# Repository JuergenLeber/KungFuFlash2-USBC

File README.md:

# Kung Fu Flash 2 USB-C

Cartridge for the Commodore 64 that packs a punch.

This repository is a fork of [KungFuFlash2-USBC](https://github.com/Sgw32/KungFuFlash2-USBC) which is a fork of an earlier version of [KungFuFlash2](https://codeberg.org/KimJorgensen/KungFuFlash2) from Kim Jørgensen that was later moved to Codeberg and is still being updated.

To have the "best of both worlds" (USB-C and updated firmware) this repository merged both of them together and additionally introduces some small fixes to the PCB and the production files.

Kung Fu Flash 2 is the big brother of [Kung Fu Flash](https://codeberg.org/KimJorgensen/KungFuFlash). It has a faster microcontroller with more memory and I/O pins, allowing for additional functionality.

**Currently, this project is considered experimental** and provides the same features as Kung Fu Flash, with these notable exceptions:

* CRT files are loaded into RAM, not flash, making large CRT files startup faster. However, changes to EasyFlash cartridges are lost if power is turned off, unless saved via the menu first
* The cartridge detects if the C64/C128 is reset. This allows the use of an additional reset button on the C64 or the built-in reset button on the C128
* REU emulation has been added

Kung Fu Flash 2 can emulate different cartridge types, load PRG files and use D64 disk images.
Just place your desired CRT, PRG or D64 files on a FAT formatted microSD card and use the built-in launcher to execute them.

## Hardware

There are three buttons on the cartridge; a reset button, a menu button for starting the launcher, and a special button that is used by the freezer cartridges.

A very nice case has been designed by [Bigby](https://www.printables.com/@Bigby) and can be found on [Printables](https://www.printables.com/model/119330-kung-fu-flash-cartridge-case).

(Picture shows the old version and will be updated as soon as the new prototypes arrive)

The gerber files and BOM can be found [here](./hardware/gerber/).

## Supported Cartridges

The following cartridge types are currently supported:

* Generic cartridge (8k, 16k, Ultimax)
* Action Replay v4.x/v5/v6
* KCS Power Cartridge
* Final Cartridge III(+)
* Simons' BASIC
* Fun Play, Power Play
* Super Games
* Ocean type 1
* Epyx Fastload
* C64 Game System, System 3
* WarpSpeed
* Dinamic
* Zaxxon, Super Zaxxon
* Magic Desk, Domark, HES Australia
* Super Snapshot v5
* Comal-80
* Ross
* EasyFlash
* Prophet64
* Freeze Frame
* Freeze Machine
* MACH 5
* Pagefox
* RGCD, Hucky
* Drean
* C128 Generic cartridge (external function ROM)
* WarpSpeed 128

## Supported File Types

The following file types are currently supported:

* Cartridge (CRT)
* C64/C128 generic cartridge (ROM, BIN)
* Disk image (D64, D71, D81)
* Tape image (T64)
* Program (PRG, P00)
* SID tune (SID)
* Firmware update (UPD)
* Text document (TXT, NFO, 1ST)

## SID Playback

SID tunes can be played directly from the launcher. This feature is inherited from the
[KungFuFlash2-USBC](https://github.com/Sgw32/KungFuFlash2-USBC) fork and is not part of the original Kung Fu Flash 2.

Selecting a SID file in the file options menu offers two actions:

* "Play" (RETURN) converts the tune and starts it immediately
* "Convert to PRG" (SHIFT+RETURN) writes a PRG file next to the SID file and returns to the launcher

In both cases the tune is converted to a PRG containing a small BASIC starter and a raster interrupt player,
so the resulting file can also be used on any other C64 setup. As the PRG is written to the microSD card,
the card must not be write protected.

PSID and RSID files of version 1 to 3 are supported, with these limitations:

* Only the first subtune is played; the tune and subtune information from the SID header is ignored
* The player uses a single speed raster interrupt, so multi speed tunes will play at the wrong tempo
* Tunes that load below $0843 cannot be converted, as this area is occupied by the BASIC starter and the player

## REU Emulation

Kung Fu Flash 2 can emulate a 1 Mb REU (RAM Expansion Unit) simultaneously with disk drive emulation.
The REU is enabled in the settings menu (F5) and active when:

* A program is executed using the default option (RETURN)
* A disk image or directory is mounted using "Mount" in the file options menu (SHIFT+RETURN)
* BASIC is started via F6 (C128) or F7 (C64) in the launcher

The REU will not be active when emulating cartridges (CRT files)

## USB Port

The USB port allows programs or disk images to be transferred from/to a PC using the EasyFlash 3 USB protocol.
The USB port is active when:

* The Kung Fu Flash 2 launcher is running
* A program is started using "Load" in the file options menu (SHIFT+RETURN)
* BASIC is started via F7 in the launcher **and** REU emulation is disabled in the settings menu (F5)

Kung Fu Flash 2 shows up as a standard serial port when connected to a PC not requiring any custom drivers to be installed.
This means, however, that the EasyFlash 3 program on the PC side must be modified to support Kung Fu Flash.

The repository of the original Kung Fu Flash contains a modified version of [EasyFlash 3 USB Utilities](https://codeberg.org/KimJorgensen/KungFuFlash/src/branch/master/3rd_party/ef3utils)
and [EasyFlash 3 BBS](https://codeberg.org/KimJorgensen/KungFuFlash/src/branch/master/3rd_party/ef3bbs) which will also work with the Kung Fu Flash 2.

## Firmware Update

Just place the KungFuFlash2_v2.xx.upd file on the SD card and select the file in the launcher to initiate the firmware update.
The newest firmware can be found [here](https://github.com/JuergenLeber/KungFuFlash2-USBC/releases).

For initial firmware installation, [see here](firmware/README.md).

## Limitations

Kung Fu Flash 2 is a so called Software Defined Cartridge where a fast microcontroller emulates cartridge hardware in software.
This makes it extremely flexible, allowing different cartridge types to be supported at a relative low cost.

However, it can be challenging to get the C64 bus timing correct in software and in some places the timing is very close to the limit.
Even though Kung Fu Flash 2 has been tested on different models of the Commodore 64, there is a chance that it doesn't work correctly on your specific model, or requires [phi2 offset adjustment](firmware/README.md#diagnostic).
Use it at your own risk!

Kung Fu Flash 2 will work with the PAL and NTSC version of the Commodore 64 or Commodore 128.

Disk drive emulation is using kernal vectors and will not work with fast loaders or software that uses direct hardware access which a lot of games does.
Currently REL files are not supported and only a subset of the Commodore DOS commands are supported.

## Thanks

Kung Fu Flash 2 was based on or uses other open source projects:

* [Kung Fu Flash](https://codeberg.org/KimJorgensen/KungFuFlash)
* [EasyFlash 3](https://bitbucket.org/skoe/easyflash) by Thomas Giesel
* [Draco Browser](https://csdb.dk/release/?id=89910) by Sascha Bader
* [fatfs-stm32](https://github.com/colosimo/fatfs-stm32) by Aurelio Colosimo
* [FatFs](http://elm-chan.org/fsw/ff/00index_e.html) by ChaN
* [libusb_stm32](https://github.com/dmitrystu/libusb_stm32) by Dmitry Filimonchuk
* [OpenC64Cart](https://github.com/SukkoPera/OpenC64Cart) by Giorgioggì
* [Disk2easyflash](https://csdb.dk/release/?id=150323) by ALeX Kazik

and a few others. Please check the individual files for their license.

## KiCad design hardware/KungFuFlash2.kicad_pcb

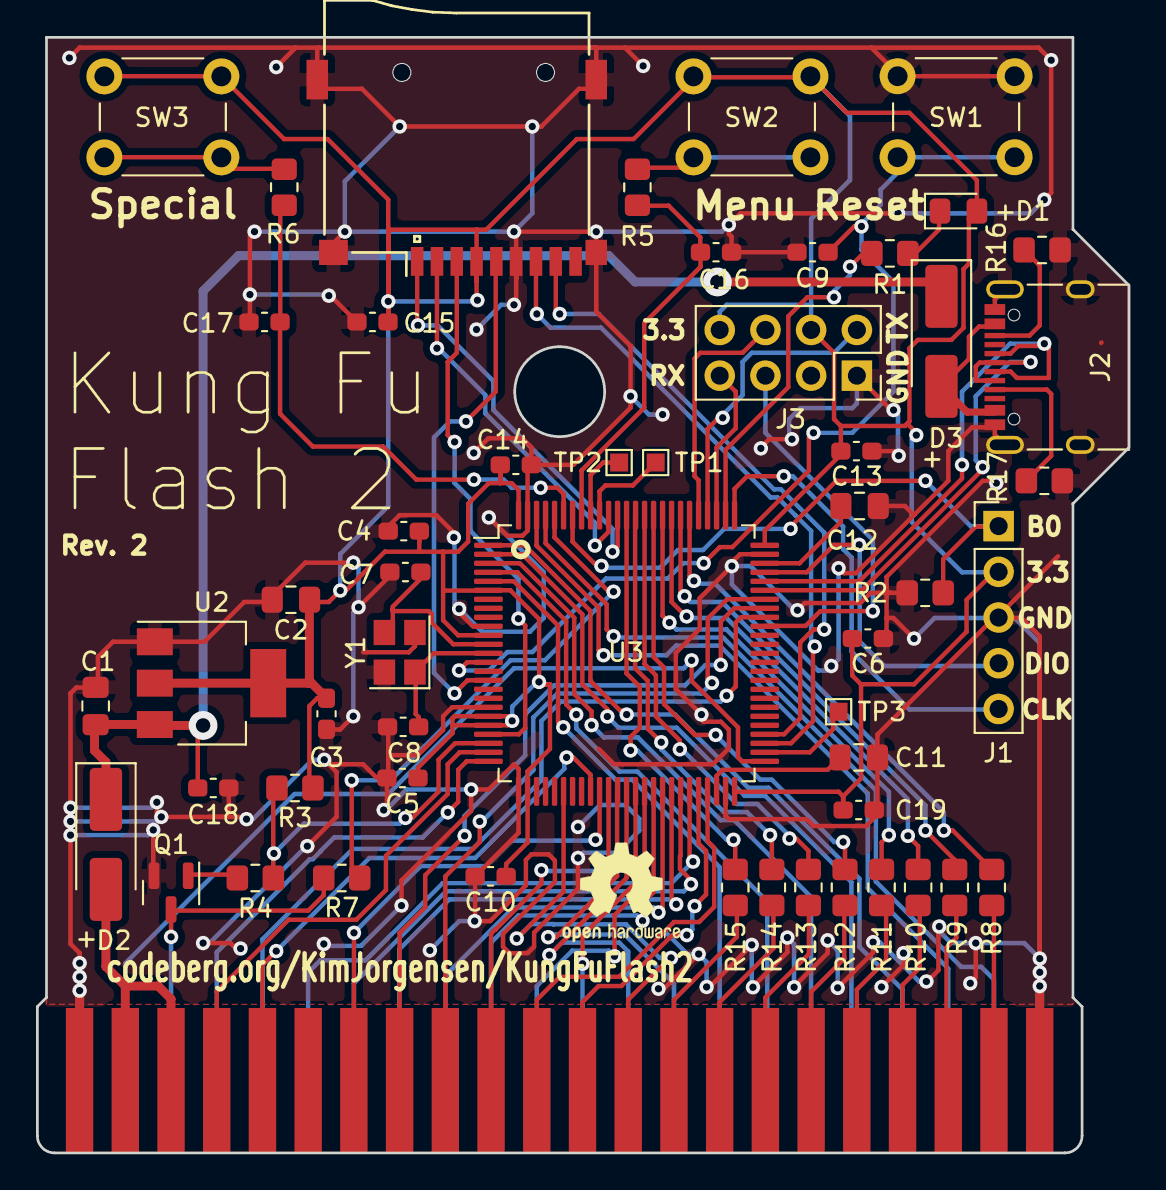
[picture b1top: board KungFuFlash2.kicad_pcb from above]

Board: 2 copper layers, 60.6 x 62.0 mm, 54 parts (0 on the bottom side), 84 nets.

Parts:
C1, C2: 10u; C_0805_2012Metric_Pad1.18x1.45mm_HandSolder
C3, C4, C5, C6, C9, C10, C13, C14, C15, C16, C17, C18, C19: 100n; C_0603_1608Metric_Pad1.08x0.95mm_HandSolder
C7, C8: 20p; C_0603_1608Metric_Pad1.08x0.95mm_HandSolder
C11, C12: 2.2u; C_0805_2012Metric_Pad1.18x1.45mm_HandSolder
D1: LED; LED_0805_2012Metric_Pad1.15x1.40mm_HandSolder
D2, D3: D_Schottky; D_SMA_Handsoldering
J1: SWD; PinHeader_1x05_P2.54mm_Vertical
J2: USB_C_Receptacle_USB2.0; USB_C_Receptacle_XKB_U262-16XN-4BVC11
J3: Wifi; PinSocket_2x04_P2.54mm_Vertical
Q1: BC817; SOT-23
R1, R4, R5, R6, R7: 510R; R_0805_2012Metric_Pad1.20x1.40mm_HandSolder
R2, R3: 10k; R_0805_2012Metric_Pad1.20x1.40mm_HandSolder
R8, R9, R10, R11, R12, R13, R14, R15: 100R; R_0805_2012Metric_Pad1.20x1.40mm_HandSolder
R16, R17: 5.1k; R_0805_2012Metric_Pad1.20x1.40mm_HandSolder
SW1: Reset; SW_PUSH_6mm_H8mm
SW2: Menu; SW_PUSH_6mm_H8mm
SW3: Special; SW_PUSH_6mm_H8mm
TP1, TP2, TP3: TestPoint_Pad_1.0x1.0mm
U1: C64-Exp-Port; C64-Cart
U2: AMS1117-3.3; SOT-223-3_TabPin2
U3: STM32H7B0VBTx; LQFP-100_14x14mm_P0.5mm
XS1: uSD_push_push; Conn_uSDcard
Y1: 25 MHz; Crystal_SMD_3225-4Pin_3.2x2.5mm

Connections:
+3V3: C2.1, C3.1, C4.1, C5.1, C6.1, C10.1, C13.1, C14.1, C15.1, C19.1, D1.2 (A), J1.2, J3.4, J3.8, R3.1, SW2.1, SW3.1, U2.2 (VO), U3.6 (VBAT), U3.11 (VDD), U3.20 (VREF+), U3.21 (VDDA), U3.27 (VDD), U3.50 (VDD), U3.75 (VDD), U3.100 (VDD), XS1.4 (Vdd)
+5C: D3.2 (A), J2.A4 (VBUS), J2.A9 (VBUS), J2.B4 (VBUS), J2.B9 (VBUS)
+5V: D2.2 (A), U1.2 (+5V), U1.3 (+5V)
/A0: U1.Y (A0), U3.97 (PE0)
/A1: U1.X (A1), U3.98 (PE1)
/A2: U1.W (A2), U3.1 (PE2)
/A3: U1.V (A3), U3.2 (PE3)
/A4: U1.U (A4), U3.3 (PE4)
/A5: U1.T (A5), U3.4 (PE5)
/A6: U1.S (A6), U3.5 (PE6)
/A7: U1.R (A7), U3.37 (PE7)
/A8: U1.P (A8), U3.38 (PE8)
/A9: U1.N (A9), U3.39 (PE9)
/A10: U1.M (A10), U3.40 (PE10)
/A11: U1.L (A11), U3.41 (PE11)
/A12: U1.K (A12), U3.42 (PE12)
/A13: U1.J (A13), U3.43 (PE13)
/A14: U1.H (A14), U3.44 (PE14)
/A15: U1.F (A15), U3.45 (PE15)
/BA: U1.12 (BA), U3.46 (PB10)
/BOOT0: J1.1, R2.1, U3.94 (BOOT0)
/CD0: R8.1, U1.21 (D0)
/CD1: R9.1, U1.20 (D1)
/CD2: R10.1, U1.19 (D2)
/CD3: R11.1, U1.18 (D3)
/CD4: R12.1, U1.17 (D4)
/CD5: R13.1, U1.16 (D5)
/CD6: R14.1, U1.15 (D6)
/CD7: R15.1, U1.14 (D7)
/D0: R8.2, U3.81 (PD0)
/D1: R9.2, U3.82 (PD1)
/D2: R10.2, U3.83 (PD2)
/D3: R11.2, U3.84 (PD3)
/D4: R12.2, U3.85 (PD4)
/D5: R13.2, U3.86 (PD5)
/D6: R14.2, U3.87 (PD6)
/D7: R15.2, U3.88 (PD7)
/MENU: C16.1, R5.2, U3.93 (PB7)
/PHI2: U1.E (PHI2), U3.67 (PA8)
/R~W: U1.5 (R-/W), U3.34 (PB0)
/SD_CK: U3.16 (PC1), XS1.5 (CLK)
/SD_CMD: U3.22 (PA0), XS1.3 (DI/CMD)
/SD_D0: U3.53 (PB14), XS1.7 (DO/DAT0)
/SD_D1: U3.54 (PB15), XS1.8 (DAT1)
/SD_D2: U3.89 (PB3), XS1.1 (DAT2)
/SD_D3: U3.90 (PB4), XS1.2 (CS/DAT3)
/SPECIAL: C17.1, R6.2, U3.95 (PB8)
/SWCLK: J1.5, U3.76 (PA14)
/SWDIO: J1.4, U3.72 (PA13)
/USB_DM: J2.A7 (D-), J2.B7 (D-), U3.70 (PA11)
/USB_DP: J2.A6 (D+), J2.B6 (D+), U3.71 (PA12)
/W_PRG: J3.5, U3.66 (PC9)
/W_RST: J3.6, U3.80 (PC12)
/W_RX: J3.2, U3.79 (PC11)
/W_TX: J3.7, U3.78 (PC10)
/~DMA: U1.13 (/DMA), U3.31 (PA7)
/~EXROM: U1.9 (/EXROM), U3.69 (PA10)
/~GAME: U1.8 (/GAME), U3.68 (PA9)
/~IO1: U1.7 (/I/O1), U3.35 (PB1)
/~IO2: U1.10 (/I/O2), U3.36 (PB2)
/~IRQ: U1.4 (/IRQ), U3.24 (PA2)
/~LED: R1.1, U3.77 (PA15)
/~NMI: U1.D (/NMI), U3.25 (PA3)
/~RESET: Q1.3 (C), R7.2, U1.C (/RESET)
/~ROMH: U1.B (/ROMH), U3.51 (PB12)
/~ROML: U1.11 (/ROML), U3.47 (PB11)
/~RST_I: R7.1, U3.96 (PB9)
/~RST_O: R3.2, R4.2, U3.23 (PA1)
/~RST: C9.1, SW1.2, U3.14 (NRST)
GND: C1.2, C2.2, C3.2, C4.2, C5.2, C6.2, C7.1, C8.1, C9.2, C10.2, C11.1, C12.2, C13.2, C14.2, C15.2, C16.2, C17.2, C18.2, C19.2, J1.3, J2.A1 (GND), J2.A12 (GND), J2.B1 (GND), J2.B12 (GND), J2.S1 (SHIELD), J3.1, Q1.2 (E), R2.2, R16.1, R17.1, SW1.1, U1.1 (GND), U1.22 (GND), U1.A (GND), U1.Z (GND), U2.1 (GND), U3.10 (VSS), U3.19 (VSSA), U3.26 (VSS), U3.49 (VSS), U3.74 (VSS), U3.99 (VSS), XS1.6 (GND), Y1.2, Y1.4
unnamed: C11.2, U3.48 (VCAP)
unnamed: C12.1, U3.73 (VCAP)
unnamed: D1.1 (K), R1.2
unnamed: C1.1, C18.1, D2.1 (K), D3.1 (K), U2.3 (VI)
unnamed: J2.A5 (CC1), R17.2
unnamed: J2.B5 (CC2), R16.2
unnamed: Q1.1 (B), R4.1
unnamed: R5.1, SW2.2
unnamed: R6.1, SW3.2
unnamed: TP1.1, U3.91 (PB5)
unnamed: TP2.1, U3.92 (PB6)
unnamed: TP3.1, U3.52 (PB13)
unnamed: C7.2, U3.12 (PH0), Y1.3
unnamed: C8.2, U3.13 (PH1), Y1.1

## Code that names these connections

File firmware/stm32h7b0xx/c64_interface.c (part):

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#include "c64_interface.h"

/******************************************************************************
* C64 address bus on PE0-PE15
******************************************************************************/
static void c64_address_config(void)
{
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}

/******************************************************************************
* C64 data bus on PD0-PD7
******************************************************************************/
static void c64_data_config(void)
{
    // Make PD0-PD7 input
    C64_DATA_INPUT();
}

/******************************************************************************
* C64 control bus on PB0-PB2 and PB10-PB12
******************************************************************************/
static void c64_control_config(void)
{
    // Release write signal PB0
    C64_CONTROL_WRITE(C64_WRITE_HIGH);

    // Set PB0 as open-drain
    GPIOB->OTYPER |= GPIO_OTYPER_OT0;

    // Make PB0 output
    MODIFY_REG(GPIOB->MODER, GPIO_MODER_MODE0, GPIO_MODER_MODE0_0);

    // Make PB1-PB2 and PB10-PB12 input
    GPIOB->MODER &= ~(GPIO_MODER_MODE1|GPIO_MODER_MODE2|GPIO_MODER_MODE10|
                      GPIO_MODER_MODE11|GPIO_MODER_MODE12);

    // No pull-up, pull-down on PB0-PB2 and PB10-PB12
    GPIOB->PUPDR &= ~(GPIO_PUPDR_PUPD0|GPIO_PUPDR_PUPD1|GPIO_PUPDR_PUPD2|
                      GPIO_PUPDR_PUPD10|GPIO_PUPDR_PUPD11|GPIO_PUPDR_PUPD12);
}
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}

/******************************************************************************
* C64 IRQ and NMI on PA2 & PA3
* C64 DMA, GAME, and EXROM on PA7 & PA9-PA10
* Status LED on PA15
******************************************************************************/
static void c64_crt_config(void)
{
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    C64_CRT_CONTROL(STATUS_LED_OFF|C64_IRQ_NMI_HIGH|C64_DMA_HIGH|C64_GAME_HIGH|
                    C64_EXROM_HIGH);

    // Set PA2-PA3 & PA7 & PA9-PA10 as open-drain
    GPIOA->OTYPER |= GPIO_OTYPER_OT2|GPIO_OTYPER_OT3|GPIO_OTYPER_OT7|
                     GPIO_OTYPER_OT9|GPIO_OTYPER_OT10;

    // Set PA2-PA3 & PA7 & PA9-PA10 as output
    MODIFY_REG(GPIOA->MODER, GPIO_MODER_MODE2|GPIO_MODER_MODE3|
                             GPIO_MODER_MODE7|GPIO_MODER_MODE9|
                             GPIO_MODER_MODE10|GPIO_MODER_MODE15,
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}

/******************************************************************************
* C64 clock input on PA8 (timer 1)
* C64 clock is 0.985 MHz (PAL) / 1.023 MHz (NTSC)
******************************************************************************/
static void c64_clock_config()
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    RCC->APB2ENR |= RCC_APB2ENR_TIM1EN;
    (void)RCC->APB2ENR;

    // Set PA8 as alternate mode 1 (TIM1_CH1)
    MODIFY_REG(GPIOA->AFR[1], GPIO_AFRH_AFSEL8, GPIO_AFRH_AFSEL8_0);
    MODIFY_REG(GPIOA->MODER, GPIO_MODER_MODE8, GPIO_MODER_MODE8_1);

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}

/******************************************************************************
* C64 reset on PA1
******************************************************************************/
static void c64_reset(void)
{
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{
    c64_reset();

    // Set PA1 as output
    MODIFY_REG(GPIOA->MODER, GPIO_MODER_MODE1, GPIO_MODER_MODE1_0);
}

/******************************************************************************
* Menu button and special button on PB7 & PB8
* C64 reset detect on PB9
******************************************************************************/
static u32 button_pressed(void)
{
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
static void menu_button_enable(void)
{
    // Enable PB7 interrupt
    EXTI->PR1 = EXTI_PR1_PR7;
    EXTI->IMR1 |= EXTI_IMR1_IM7;
}

static void button_config(void)
{
    // Make PB7-PB9 input
    GPIOB->MODER &= ~(GPIO_MODER_MODE7|GPIO_MODER_MODE8|GPIO_MODER_MODE9);

    // Enable pull-down on PB7 and PB8
    MODIFY_REG(GPIOB->PUPDR, GPIO_PUPDR_PUPD7|GPIO_PUPDR_PUPD8,
                             GPIO_PUPDR_PUPD7_1|GPIO_PUPDR_PUPD8_1);

    // Rising edge trigger on PB7 and falling edge trigger on PB9
    MODIFY_REG(EXTI->RTSR1, EXTI_RTSR1_TR7|EXTI_RTSR1_TR9, EXTI_RTSR1_TR7);
    MODIFY_REG(EXTI->FTSR1, EXTI_FTSR1_TR7|EXTI_FTSR1_TR9, EXTI_FTSR1_TR9);

    // EXTI7 interrupt on PB7
    MODIFY_REG(SYSCFG->EXTICR[1], SYSCFG_EXTICR2_EXTI7, SYSCFG_EXTICR2_EXTI7_PB);

    // EXTI9 interrupt on PB9
    MODIFY_REG(SYSCFG->EXTICR[2], SYSCFG_EXTICR3_EXTI9, SYSCFG_EXTICR3_EXTI9_PB);

    // Enable EXTI9_5_IRQHandler, lowest priority
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
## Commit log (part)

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2025-12-18 Move to Codeberg
2026-01-17 Less restrictive frequency check
2026-04-11 Reset to menu via USB (from KFF v1.54)
2026-06-05 Reduce firmware size
2026-06-06 Add FAT sorting (from KFF v1.55)

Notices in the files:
firmware/stm32h7b0xx/c64_interface.c:
Copyright (c) 2019-2024 Kim Jørgensen
